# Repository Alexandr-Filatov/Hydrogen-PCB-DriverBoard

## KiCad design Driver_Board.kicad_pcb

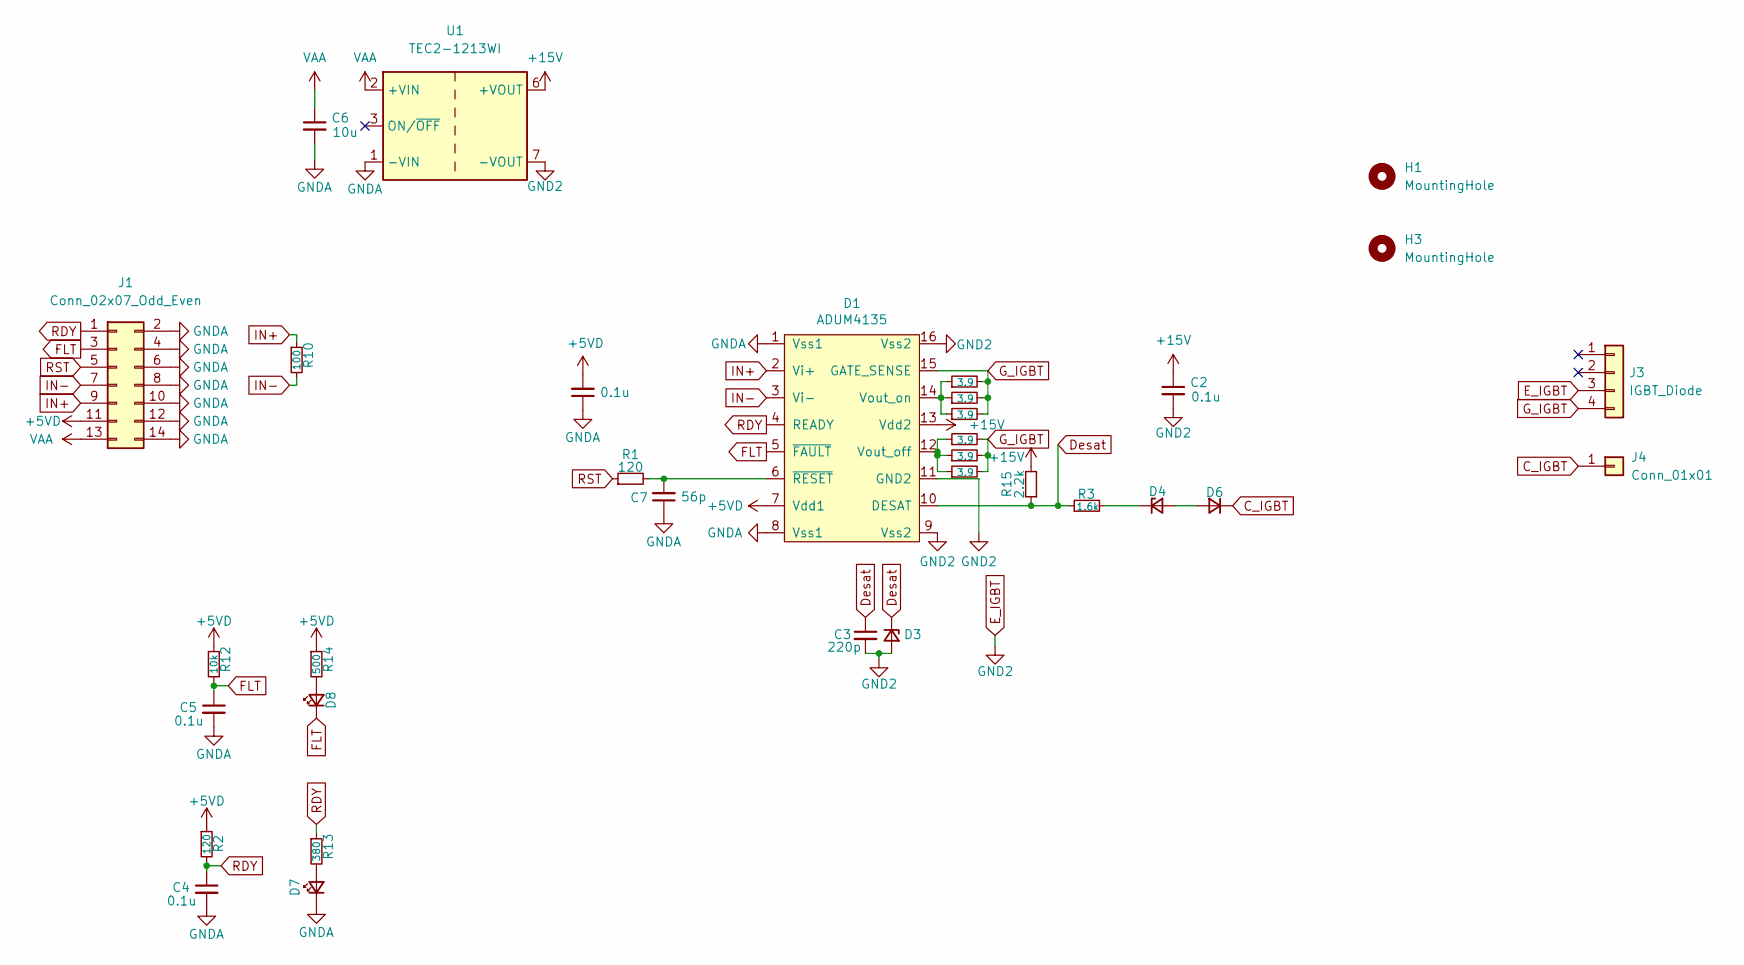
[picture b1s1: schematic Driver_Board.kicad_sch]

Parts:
C1, C2, C4, C5: 0.1u; C_0805_2012Metric_Pad1.18x1.45mm_HandSolder
C3: 220p; C_0805_2012Metric_Pad1.18x1.45mm_HandSolder
C6: 10u; C_1210_3225Metric_Pad1.33x2.70mm_HandSolder
C7: 56p; C_0805_2012Metric_Pad1.18x1.45mm_HandSolder
D1: ADUM4135; SOIC-16W_7.5x10.3mm_P1.27mm
D3, D4: BZT52C10-7-F; D_SOD-123
D6: MURS360T3G; D_SMA_Handsoldering
D7, D8: LED_Small; LED_0805_2012Metric_Pad1.15x1.40mm_HandSolder
H1, H3: MountingHole; MountingHole_3.2mm_M3
J1: Conn_02x07_Odd_Even; IDC-Header_2x07-1MP_P2.54mm_Latch_Vertical
J3: IGBT_Diode; IGBT_Gate
J4: Conn_01x01; Wire
R1, R2: 120; R_0805_2012Metric_Pad1.20x1.40mm_HandSolder
R3: 1.6k; R_1206_3216Metric_Pad1.30x1.75mm_HandSolder
R4, R5, R6, R7, R8, R9: 3.9; R_1206_3216Metric_Pad1.30x1.75mm_HandSolder
R10: 100; R_0805_2012Metric_Pad1.20x1.40mm_HandSolder
R12: 10k; R_0805_2012Metric_Pad1.20x1.40mm_HandSolder
R13: 380; R_0805_2012Metric_Pad1.20x1.40mm_HandSolder
R14: 500; R_0805_2012Metric_Pad1.20x1.40mm_HandSolder
R15: 2.2k; R_0805_2012Metric_Pad1.20x1.40mm_HandSolder
U1: TEC2-1213WI; Converter_DCDC_TRACO_TMR-xxxx_THT

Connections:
+5VD: C1.2, D1.7 (Vdd1), J1.11, R2.1, R12.1, R14.1
+15V: C2.1, D1.13 (Vdd2), R15.2, U1.6 (+VOUT)
C_IGBT: D6.1 (K), J4.1
Desat: C3.1, D1.10 (DESAT), D3.1 (K), R3.1, R15.1
E_IGBT: C2.2, C3.2, D1.9 (Vss2), D1.11 (GND2), D1.16 (Vss2), D3.2 (A), J3.3, U1.7 (-VOUT)
FLT: C5.1, D1.5 (~FAULT), D8.1 (K), J1.3, R12.2
GNDA: C1.1, C4.2, C5.2, C6.2, C7.1, D1.1 (Vss1), D1.8 (Vss1), D7.1 (K), J1.2, J1.4, J1.6, J1.8, J1.10, J1.12, J1.14, U1.1 (-VIN)
G_IGBT: D1.15 (GATE_SENSE), J3.4, R4.2, R5.2, R6.2, R7.2, R8.2, R9.2
IN+: D1.2 (Vi+), J1.9, R10.1
IN-: D1.3 (Vi-), J1.7, R10.2
unnamed: C7.2, D1.6 (~RESET), R1.2
unnamed: D1.12 (Vout_off), R5.1, R8.1, R9.1
unnamed: D1.14 (Vout_on), R4.1, R6.1, R7.1
unnamed: D4.1 (K), R3.2
unnamed: D4.2 (A), D6.2 (A)
unnamed: D7.2 (A), R13.2
unnamed: D8.2 (A), R14.2
RDY: C4.1, D1.4 (READY), J1.1, R2.2, R13.1
RST: J1.5, R1.1
VAA: C6.1, J1.13, U1.2 (+VIN)

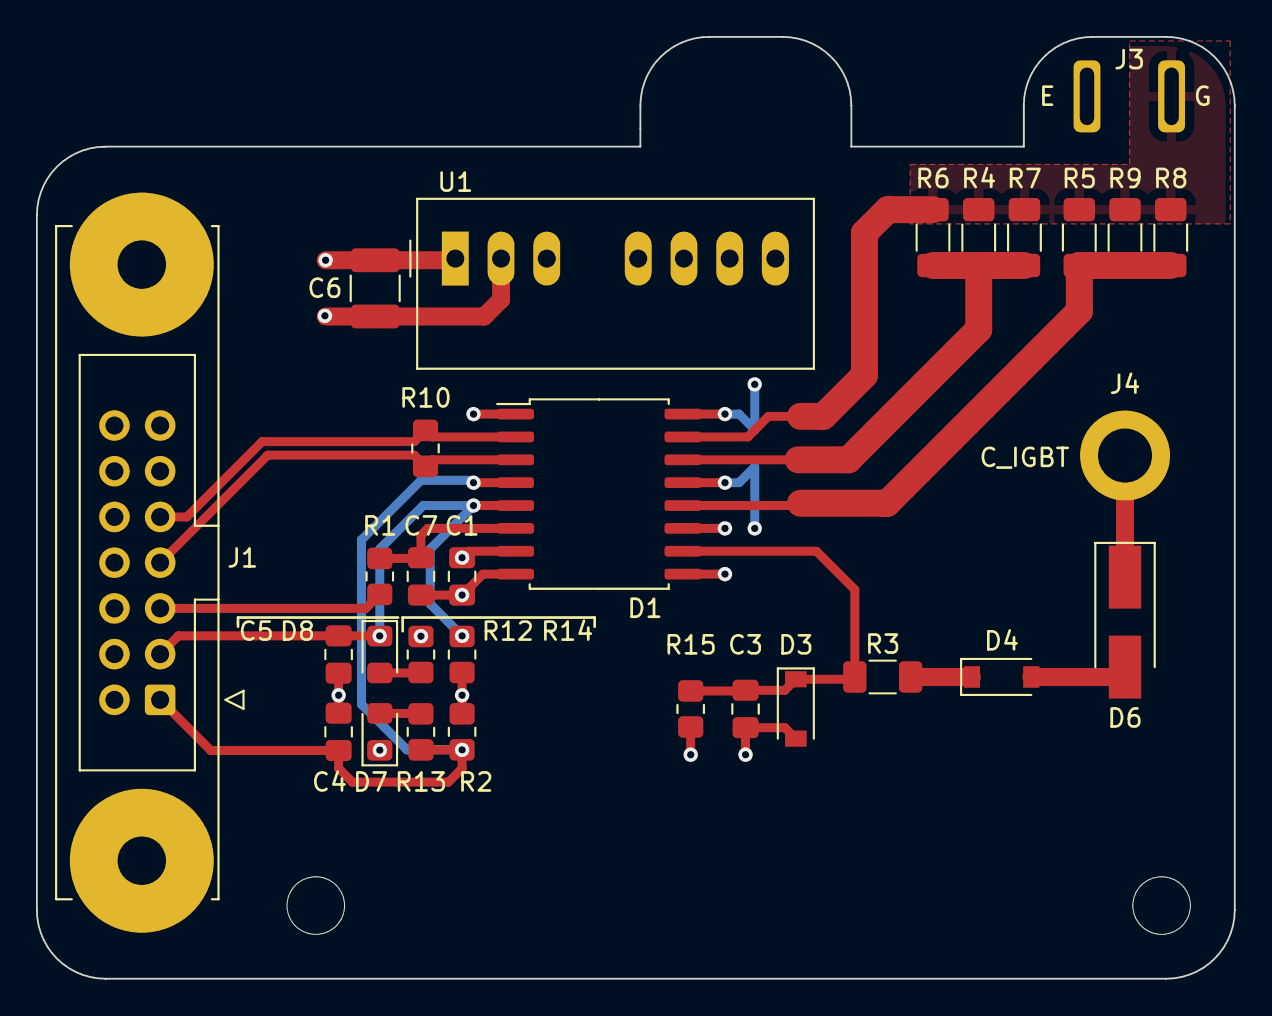
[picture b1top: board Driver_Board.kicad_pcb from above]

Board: 4 copper layers, 66.5 x 52.3 mm, 33 parts (1 on the bottom side), 20 nets.

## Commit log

2022-05-18 VER1.0
2022-06-24 Основа ADUM4135
2022-08-22 Плата на два модуля
2022-08-22 Первая версия в производство
2022-08-22 Добавил гербера
